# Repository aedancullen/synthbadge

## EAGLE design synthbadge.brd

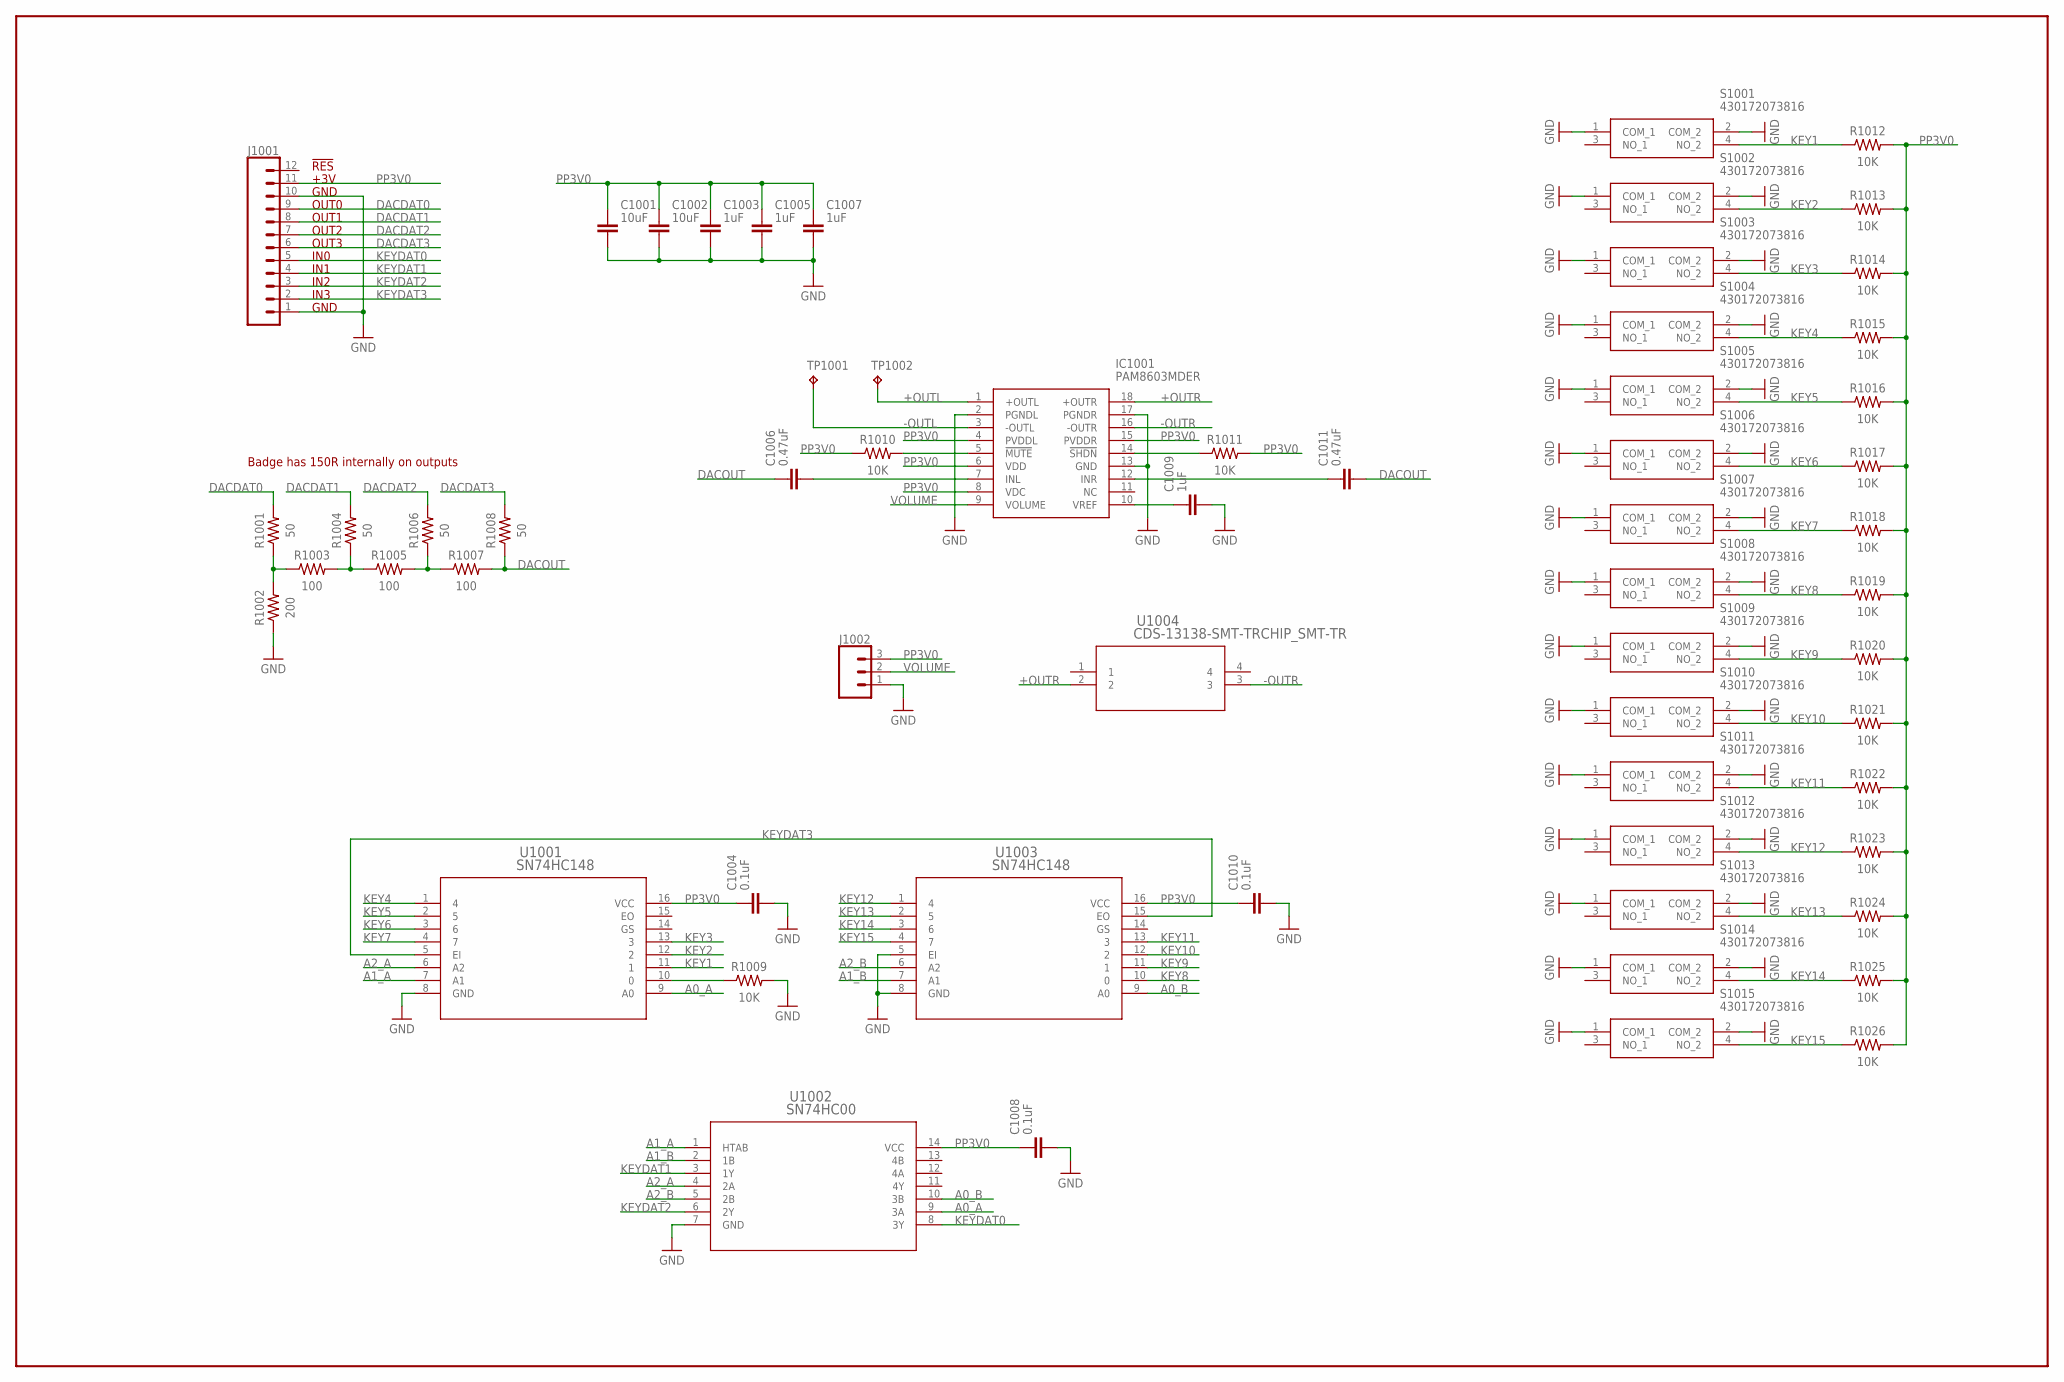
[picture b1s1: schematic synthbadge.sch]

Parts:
C1001, C1002: 10uF; CAPC2012X110
C1003, C1005, C1007, C1009: 1uF; CAPC2012X110
C1004, C1008, C1010: 0.1uF; CAPC2012X110
C1006, C1011: 0.47uF; CAPC2012X110
IC1001: PAM8603MDER; SOIC127P1032X270-18N
J1001: CONN_12; 1X12
J1002: CONN_03; 1X03
R1001, R1004, R1006, R1008: 50; RESC2012X65
R1002: 200; RESC2012X65
R1003, R1005, R1007: 100; RESC2012X65
R1009, R1010, R1011, R1012, R1013, R1014, R1015, R1016, R1017, R1018, R1019, R1020, R1021, R1022, R1023, R1024, R1025, R1026: 10K; RESC2012X65
S1001, S1002, S1003, S1004, S1005, S1006, S1007, S1008, S1009, S1010, S1011, S1012, S1013, S1014, S1015: 430172073816
TP1001, TP1002: TPB2,54; B2,54
U1001, U1003: SN74HC148; D16_TEX
U1002: SN74HC00; D14_TEX
U1004: CDS-13138-SMT-TRCHIP_SMT-TR; CHIP_SMT-TR

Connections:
+OUTL: IC1001.1 (+OUTL), TP1002.TP
+OUTR: IC1001.18 (+OUTR), U1004.2
-OUTL: IC1001.3 (-OUTL), TP1001.TP
-OUTR: IC1001.16 (-OUTR), U1004.3
A0_A: U1001.9 (A0), U1002.9 (3A)
A0_B: U1002.10 (3B), U1003.9 (A0)
A1_A: U1001.7 (A1), U1002.1 (HTAB)
A1_B: U1002.2 (1B), U1003.7 (A1)
A2_A: U1001.6 (A2), U1002.4 (2A)
A2_B: U1002.5 (2B), U1003.6 (A2)
DACDAT0: J1001.9, R1001.2
DACDAT1: J1001.8, R1004.2
DACDAT2: J1001.7, R1006.2
DACDAT3: J1001.6, R1008.2
DACOUT: C1006.1, C1011.2, R1007.2, R1008.1
GND: C1001.2, C1002.2, C1003.2, C1004.2, C1005.2, C1007.2, C1008.2, C1009.2, C1010.2, IC1001.2 (PGNDL), IC1001.13 (GND), IC1001.17 (PGNDR), J1001.1, J1001.10, J1002.1, R1002.1, R1009.2, S1001.1 (COM_1), S1001.2 (COM_2), S1002.1 (COM_1), S1002.2 (COM_2), S1003.1 (COM_1), S1003.2 (COM_2), S1004.1 (COM_1), S1004.2 (COM_2), S1005.1 (COM_1), S1005.2 (COM_2), S1006.1 (COM_1), S1006.2 (COM_2), S1007.1 (COM_1), S1007.2 (COM_2), S1008.1 (COM_1), S1008.2 (COM_2), S1009.1 (COM_1), S1009.2 (COM_2), S1010.1 (COM_1), S1010.2 (COM_2), S1011.1 (COM_1), S1011.2 (COM_2), S1012.1 (COM_1), S1012.2 (COM_2), S1013.1 (COM_1), S1013.2 (COM_2), S1014.1 (COM_1), S1014.2 (COM_2), S1015.1 (COM_1), S1015.2 (COM_2), U1001.8 (GND), U1002.7 (GND), U1003.5 (EI), U1003.8 (GND)
KEY1: R1012.1, S1001.4 (NO_2), U1001.11 (1)
KEY2: R1013.1, S1002.4 (NO_2), U1001.12 (2)
KEY3: R1014.1, S1003.4 (NO_2), U1001.13 (3)
KEY4: R1015.1, S1004.4 (NO_2), U1001.1 (4)
KEY5: R1016.1, S1005.4 (NO_2), U1001.2 (5)
KEY6: R1017.1, S1006.4 (NO_2), U1001.3 (6)
KEY7: R1018.1, S1007.4 (NO_2), U1001.4 (7)
KEY8: R1019.1, S1008.4 (NO_2), U1003.10 (0)
KEY9: R1020.1, S1009.4 (NO_2), U1003.11 (1)
KEY10: R1021.1, S1010.4 (NO_2), U1003.12 (2)
KEY11: R1022.1, S1011.4 (NO_2), U1003.13 (3)
KEY12: R1023.1, S1012.4 (NO_2), U1003.1 (4)
KEY13: R1024.1, S1013.4 (NO_2), U1003.2 (5)
KEY14: R1025.1, S1014.4 (NO_2), U1003.3 (6)
KEY15: R1026.1, S1015.4 (NO_2), U1003.4 (7)
KEYDAT0: J1001.5, U1002.8 (3Y)
KEYDAT1: J1001.4, U1002.3 (1Y)
KEYDAT2: J1001.3, U1002.6 (2Y)
KEYDAT3: J1001.2, U1001.5 (EI), U1003.15 (EO)
unnamed: C1006.2, IC1001.7 (INL)
unnamed: C1011.1, IC1001.12 (INR)
unnamed: C1009.1, IC1001.10 (VREF)
unnamed: R1009.1, U1001.10 (0)
unnamed: IC1001.14 (!SHDN), R1011.1
unnamed: IC1001.5 (!MUTE), R1010.2
unnamed: R1001.1, R1002.2, R1003.1
unnamed: R1003.2, R1004.1, R1005.1
unnamed: R1005.2, R1006.1, R1007.1
PP3V0: C1001.1, C1002.1, C1003.1, C1004.1, C1005.1, C1007.1, C1008.1, C1010.1, IC1001.4 (PVDDL), IC1001.6 (VDD), IC1001.8 (VDC), IC1001.15 (PVDDR), J1001.11, J1002.3, R1010.1, R1011.2, R1012.2, R1013.2, R1014.2, R1015.2, R1016.2, R1017.2, R1018.2, R1019.2, R1020.2, R1021.2, R1022.2, R1023.2, R1024.2, R1025.2, R1026.2, U1001.16 (VCC), U1002.14 (VCC), U1003.16 (VCC)
VOLUME: IC1001.9 (VOLUME), J1002.2

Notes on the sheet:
!RES
+3V
GND
OUT0
OUT1
OUT2
OUT3
IN0
IN1
IN2
IN3
Badge has 150R internally on outputs

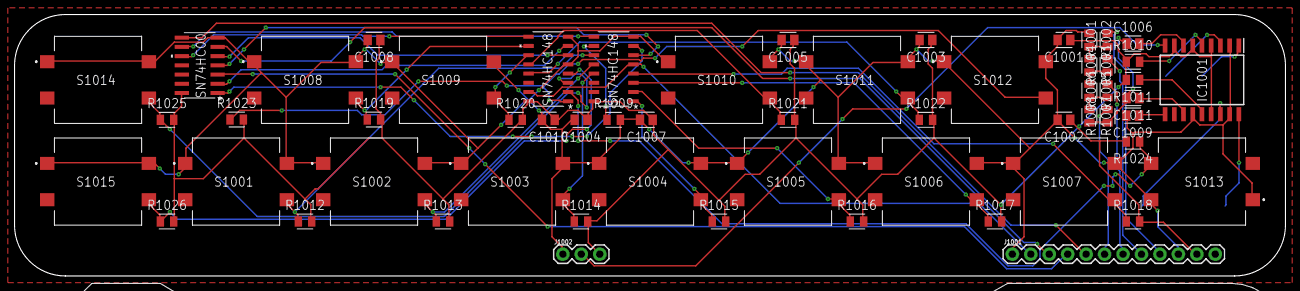
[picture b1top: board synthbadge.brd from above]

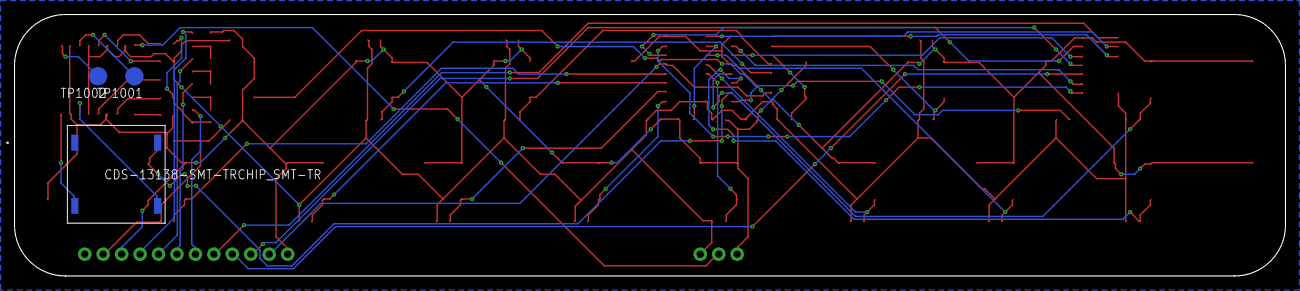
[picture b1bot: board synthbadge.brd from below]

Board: 2 copper layers, 175.0 x 36.0 mm, 61 parts (3 on the bottom side), 46 nets.

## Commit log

2022-11-03 Add STEP files
2022-11-07 Add test code (simple tones, and some layout of a wavetable in instruction mem)
2022-11-07 Add rail part for mechanically joining PCB edges

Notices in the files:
parts and their libraries:
SparkFun-Connectors: Licensing: Creative Commons ShareAlike 4.0 International - https://creativecommons.org/licenses/by-sa/4.0
COPYRIGHT: Copyright (C) 2022 Ultra Librarian. All rights reserved.
